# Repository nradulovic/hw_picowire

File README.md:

# hw_picowire
Small headphone amplifier

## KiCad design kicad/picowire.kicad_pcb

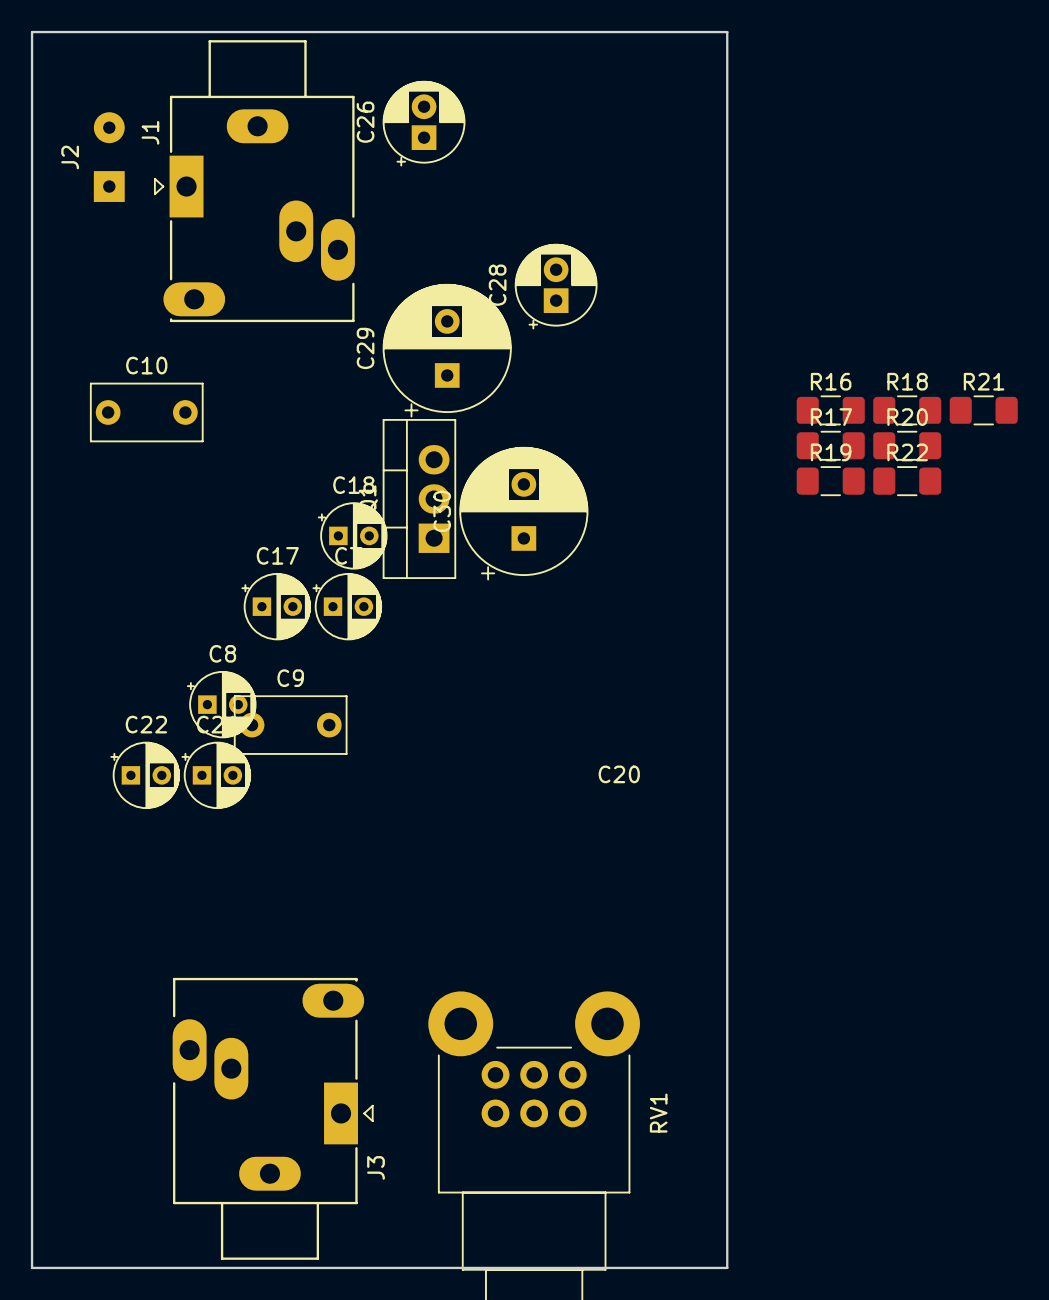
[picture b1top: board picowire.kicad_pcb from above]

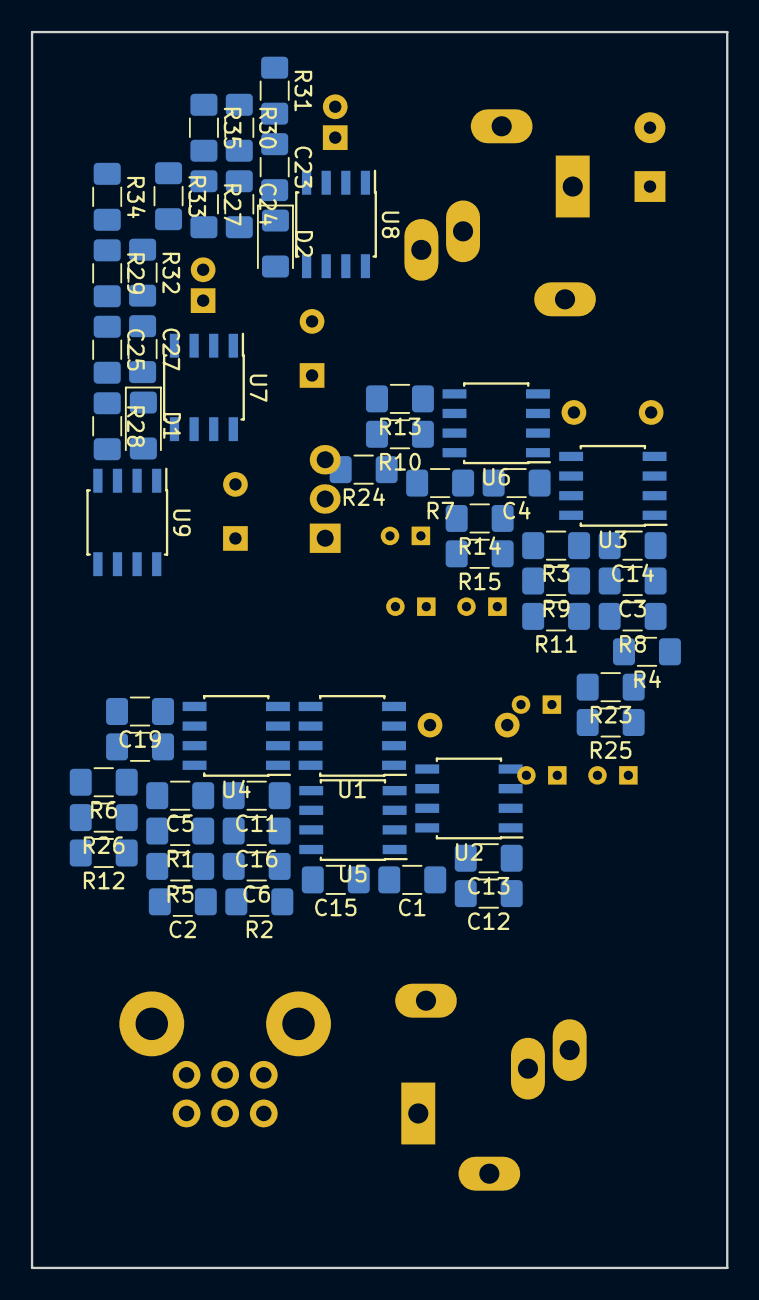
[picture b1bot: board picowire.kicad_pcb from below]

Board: 2 copper layers, 45.0 x 80.0 mm, 81 parts (57 on the bottom side), 43 nets, no tracks yet.

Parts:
C1, C2: 100p; C_1206_3216Metric_Pad1.42x1.75mm_HandSolder
C3, C4, C5, C6, C11, C12, C13, C14, C15, C16, C19, C20, C23, C24, C25, C27: 100n; C_1206_3216Metric_Pad1.42x1.75mm_HandSolder
C7, C8, C17, C18: 22u; CP_Radial_D4.0mm_P2.00mm
C9, C10: 1u; C_Rect_L7.0mm_W3.5mm_P5.00mm
C21, C22: 10u; CP_Radial_D4.0mm_P2.00mm
C26, C28: 47u; CP_Radial_D5.0mm_P2.00mm
C29, C30: 1m; CP_Radial_D8.0mm_P3.50mm
D1: 1N4007; D_1206_3216Metric_Pad1.42x1.75mm_HandSolder
D2: BZX85C22; D_1206_3216Metric_Pad1.42x1.75mm_HandSolder
J1, J3: AudioJack3_Ground; StereoJack_3.5mm_Switch_Ledino_KB3SPRS_Horizontal
J2: Jack-DC; SolderWirePad_1x02_P3.81mm_Drill0.8mm
Q1: BDX53; TO-220-3_Vertical
R1, R2: 100; R_1206_3216Metric_Pad1.42x1.75mm_HandSolder
R3, R4: 20k; R_1206_3216Metric_Pad1.42x1.75mm_HandSolder
R5, R6, R15, R16, R17, R18, R19, R20, R21, R22, R28, R29: 10k; R_1206_3216Metric_Pad1.42x1.75mm_HandSolder
R7, R8, R11, R12, R13, R14, R27: 1k; R_1206_3216Metric_Pad1.42x1.75mm_HandSolder
R9, R10: 3k; R_1206_3216Metric_Pad1.42x1.75mm_HandSolder
R23, R24, R25, R26, R30, R31, R32, R33, R34, R35: 10; R_1206_3216Metric_Pad1.42x1.75mm_HandSolder
RV1: 10k; Potentiometer_Alps_RK09L_Double_Horizontal
U1, U3, U5, U6: NE5532; SOIC-8_3.9x4.9mm_P1.27mm
U2, U4, U7, U8, U9: OPA1688; SOIC-8_3.9x4.9mm_P1.27mm

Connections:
/pamp/output_left: R23.1, R24.1
/pamp/output_right: R25.1, R26.1
/psupply/ps_pos: D1.2, J2.2
GNDA: C1.2, C2.2, C3.2, C4.1, C5.2, C6.1, C7.2, C8.1, C11.2, C12.1, C13.2, C14.1, C15.2, C16.1, C17.2, C18.1, C19.2, C20.1, C29.2, C30.1, R3.2, R4.2, R5.2, R6.2, R15.2, R16.2, R17.2, R18.2, R30.1, R31.1, R32.1, R33.1, R34.1, R35.1, U1.5, U3.5, U5.5, U6.5
unnamed: C1.1, C9.2, R1.1, R3.1
unnamed: C9.1, R5.1, U1.3
unnamed: C10.1, R6.1, U3.3
unnamed: C2.1, C10.2, R2.1, R4.1
unnamed: C21.1, R15.1, R16.1, U2.3, U2.5
unnamed: C21.2, R13.1, U5.7
unnamed: C22.1, R17.1, R18.1, U4.3, U4.5
unnamed: C22.2, R14.1, U6.7
unnamed: C24.1, D1.1, Q1.2, R27.1
unnamed: C26.1, D2.1, Q1.1, R27.2
unnamed: R7.1, R9.2, U1.6
unnamed: R7.2, U5.1, U5.2
unnamed: R8.2, U6.1, U6.2
unnamed: R10.1, R12.2, RV1.4, U3.7
unnamed: R8.1, R10.2, U3.6
unnamed: R11.1, R13.2, U5.6
unnamed: R9.1, R11.2, RV1.1, U1.7
unnamed: R12.1, R14.2, U6.6
unnamed: R19.1, R23.2, U2.1
unnamed: R19.2, U2.2
unnamed: R20.1, R24.2, U2.7
unnamed: R20.2, U2.6
unnamed: R21.1, R25.2, U4.1
unnamed: R21.2, U4.2
unnamed: R22.1, R26.2, U4.7
unnamed: R22.2, U4.6
unnamed: R28.2, R29.1, U7.3, U7.5, U8.3, U8.5, U9.3, U9.5
unnamed: R30.2, U7.1, U7.2
unnamed: R31.2, U7.6, U7.7
unnamed: R32.2, U8.1, U8.2
unnamed: R33.2, U8.6, U8.7
unnamed: R34.2, U9.1, U9.2
unnamed: R35.2, U9.6, U9.7
unnamed: RV1.2, U5.3
unnamed: RV1.3, U1.1, U1.2
unnamed: RV1.5, U6.3
unnamed: RV1.6, U3.1, U3.2
VCC: C3.1, C5.1, C7.1, C11.1, C13.1, C15.1, C17.1, C19.1, C23.1, C25.1, C27.1, C28.1, C29.1, Q1.3, R28.1, U1.8, U2.8, U3.8, U4.8, U5.8, U6.8, U7.8, U8.8, U9.8
VEE: C4.2, C6.2, C8.2, C12.2, C14.2, C16.2, C18.2, C20.2, C23.2, C24.2, C25.2, C26.2, C27.2, C28.2, C30.2, D2.2, J2.1, R29.2, U1.4, U2.4, U3.4, U4.4, U5.4, U6.4, U7.4, U8.4, U9.4

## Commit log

2018-10-17 Removing files that should be ignored.
2019-01-08 Update.
2020-04-22 Project update
